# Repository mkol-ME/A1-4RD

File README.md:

# A1-4RD — "Alfred"

A 3D-printed desk companion with a moving jaw and a voice, written in the manner of an old-fashioned
butler: dry, warm, terse, and genuinely useful. Not a smart speaker.

Everything runs locally. A laptop (later a Raspberry Pi inside the printed body) is the face: microphone,
speaker, wake word. A headless Ubuntu box on the LAN is the brain: speech recognition, memory, web lookup,
the language model and his voice. Nothing is sent to a hosted service.

> **The character is the project. Everything else is plumbing.**

## What I built, and what I learned

I built a voice assistant with a fixed personality that runs entirely on my own hardware: speech detection
and wake word on a laptop, and Whisper, a 26-billion-parameter language model, long-term memory, web and
weather lookup and a custom synthesized voice on a home server. That server runs on a secondhand datacenter
GPU I had to reflash and coax into a consumer motherboard. Through measurement rather than guesswork, I got
a spoken reply's first sound down to about 1.15 seconds, and a web-searched answer from 7.1 to 3.5 seconds.
The biggest lesson was that intuition is unreliable with language models. Adding rules to the prompt made
the character worse three separate times. My first test suite passed while the real failures went
undetected, because its questions had leaked into the training examples. Two confident theories about why
he rambled both turned out wrong. So I built a held-out evaluation that checks its own contamination, and
changed things only when a number moved. I also learned to put boundaries in code rather than instructions:
anything that reaches the prompt will eventually be said out loud, so access to memory has to be enforced in
the database query itself.

## The physical build

The body is fully modelled in CAD; it has not been printed or assembled yet.

- **Printed body** ([`hardware/cad/mechanical/rev-b`](hardware/cad/mechanical/rev-b)): sixteen parts as STEP
  solids and millimetre STL, 202 mm tall. The chin is a separate part, driven by a servo through a drive
  link, so the jaw can move while he speaks.
- **Electronics layout** ([`hardware/cad/mechanical/modules-rev-a`](hardware/cad/mechanical/modules-rev-a)):
  a tray and fit models for off-the-shelf boards — Raspberry Pi, I²S microphone, amplifier, servo driver and
  USB-C power.
- **Custom carrier PCB** ([`hardware/cad/pcb/rev-e`](hardware/cad/pcb/rev-e)): a four-layer KiCad board for a
  Pi Zero 2 W, an ICS-43434 microphone, a MAX98357A amplifier and the jaw servo, with a latching power-fault
  cutoff. Gerbers, drill files, BOM and DRC/ERC reports are included; revisions C to E are kept. Not yet
  fabricated.

The STEP files open in SolidWorks, Fusion or FreeCAD. [`hardware/cad/README.md`](hardware/cad/README.md) maps
every revision.

---

## Contents

- [The physical build](#the-physical-build)
- [How a spoken turn works](#how-a-spoken-turn-works)
- [Hardware](#hardware)
- [Repository layout](#repository-layout)
- [Talking to Alfred](#talking-to-alfred)
- [The server](#the-server)
- [Performance](#performance)
- [Testing](#testing)
- [Status and roadmap](#status-and-roadmap)
- [Further reading](#further-reading)

---

## How a spoken turn works

```text
 LAPTOP (client/)                               SERVER (brain/, over an SSH tunnel)
 ─────────────────                              ───────────────────────────────────────────────
 microphone, 16 kHz
   → speech detection against the room's
     measured noise floor
   → at 0.20 s of silence, send audio ────────→ Whisper small.en on the GTX 1060
   → at 0.40 s, end the turn — or wait up to
     1.0 s if the words so far trail off
   → wake word / attention window
   → text ────────────────────────────────────→ voice server
                                                  → tool gate: does this need a lookup?
                                                  → decider: search memory / search web
                                                    (SearXNG, Wikipedia) / sports scores
                                                    (ESPN) / news (Google News) / remember
                                                    weather goes to Open-Meteo instead
                                                  → gemma4 26B on the MI50 via Ollama
                                                  → cut the stream into whole sentences
                                                  → Alfred's distilled Piper voice (CPU)
 speaker (WASAPI) ←──── one WAV per sentence ─── ← streamed as NDJSON
```

The pieces are deliberately separable:

| Layer | Files | Decides |
|---|---|---|
| **Character** | `persona/` (private; `.example` stand-ins here), `brain/prompts.py` | how he behaves |
| **Knowledge** | `brain/memory.py`, `brain/memory_tools.py`, `brain/web.py`, `brain/weather.py`, `brain/sports.py`, `brain/news.py`, `brain/markets.py` | what evidence he sees |
| **Transport** | `brain/voice_server.py`, `brain/whisper_server.py`, SSH | how text and audio move |
| **Embodiment** | `client/listen.py`, `client/talk.py`, later the servos | how he is present in the room |

A better voice cannot fix a bad answer, and a longer prompt cannot replace memory, so each layer is
debugged on its own.

---

## Hardware

**Server** (headless Ubuntu 24.04; setup and operation in [docs/server.md](docs/server.md))

| Part | Role |
|---|---|
| i7-8700 · 48 GB DDR4 · MSI MPG Z390 Gaming Plus | host |
| **AMD Radeon Instinct MI50 32 GB** | the language model (Ollama, Vulkan backend) |
| **NVIDIA GTX 1060 6 GB** | Whisper |
| 500 GB NVMe · 3×2 TB RAID 5 · 1.5 TB | OS and models · Alfred's memory database · spare |

The MI50 is a secondhand datacenter card. Getting it working in a consumer board took a VBIOS reflash,
*Above 4G Decoding* in the BIOS and `pci=realloc` on the kernel command line. It has no fan of its own, so a
server fan is driven from the card's temperature by [`ops/fan`](ops/fan). Two driver settings keep the whole
model in video memory; without them half of it silently spilled into system RAM, at 4 tokens a second
instead of 40 ([why each setting is there](docs/server.md#ollama-settings)).

**Client:** any Windows laptop with a microphone. Later: a Raspberry Pi in the printed body, with a servo jaw
and a neck servo — see [The physical build](#the-physical-build).

---

## Repository layout

```text
A1-4RD/
├── brain/                    runs on the server
│   ├── alfred.py             model choice, prompt assembly, streaming; also a terminal chat client
│   ├── memory.py             SQLite memory: recent conversation, facts, semantic search
│   ├── memory_tools.py       the tool decider and its tools (memory, web, facts)
│   ├── web.py                Wikipedia + SearXNG lookup, run concurrently
│   ├── sports.py             live scores, results and fixtures from ESPN
│   ├── news.py               headlines from Google News
│   ├── markets.py            live prediction-market odds from Polymarket
│   ├── machine.py            the server's own temperatures, fan, power, VRAM, RAID and disks
│   ├── weather.py            live forecast from Open-Meteo, not search snippets
│   ├── media.py              "play…" / "find videos of…" requests and spoken titles
│   ├── media_server.py       YouTube search, audio stream, chapters and captions (own venv: yt-dlp, PyAV)
│   ├── guru.py               The MMA Guru's take on a fight, from his breakdown videos
│   ├── voice_server.py       one spoken turn end to end, streamed sentence by sentence
│   ├── whisper_server.py     resident Whisper, so no model load per utterance
│   ├── audio_archive.py      every utterance kept on the array with its transcript, under a size cap
│   ├── youtube.py            what a named YouTube channel has posted, from its real upload list
│   ├── spoken.py             text rules for what is said aloud, such as which voice reads a sentence
│   ├── prompts.py            loads the private wording, or the .example stand-ins
│   └── whisper_transcribe.py one-off file transcription
├── persona/
│   ├── alfred.example.md     stand-in for alfred.md (who he is), which is kept private
│   ├── examples.example.md   stand-in for examples.md (how he talks)
│   └── prompts.example.json  stand-in for prompts.json (the instructions sent with each turn)
├── client/                   runs on the laptop
│   ├── listen.py             speak to him: wake word, attention window, early transcription
│   ├── talk.py               type to him, hear him answer; also the audio player
│   ├── music.py              plays YouTube audio; pause, stop, volume, ducking under his voice
│   └── launcher/             builds Alfred.exe, a double-click launcher
├── scripts/                  server launch scripts, and a scratch copy of the voice server for testing
├── voice-training/           how his voice was made: auditions, RVC, distillation into Piper
├── tests/                    unit tests for memory, tool gate and the listening loop
├── ops/                      server setup, version-controlled
│   ├── fan/                  MI50 fan curve service + interactive installer
│   ├── reboot/               idle-only 3 a.m. reboot every third night
│   ├── ollama/               Ollama settings and boot-time model preload
│   ├── services/             start SearXNG, Whisper and the voice server at boot
│   └── remote-access/        key-only SSH and Tailscale
├── requirements/             pinned environments (client TTS, Whisper, RVC, Qwen-TTS)
├── hardware/                 CAD (STEP/STL), KiCad PCB and bring-up notes for the body
└── docs/                     running the server, and reaching it
```

---

## Talking to Alfred

- Say **"Alfred, …"** to start. He then stays attentive for three minutes without needing his name.
  **"That'll be all"** dismisses him.
- Say his name while he is talking and he stops, so you can cut in.
- **"Play …"** asks whether you want Spotify or YouTube, then plays it through his speaker. **"Find videos
  of …"** reads out the top results. While music plays, **"Alfred, pause / resume / stop / louder / quieter"** works, and the
  music drops whenever he talks.
- Ask about the weather, last night's game, the news, or something you told him last week. He decides
  on his own when a question needs a lookup.
- Typing works too: the same conversation and memory, without the audio.

Running the client and the server is covered in [docs/server.md](docs/server.md).

---

## Performance

Measured 2026-09-16, from the end of speech to Alfred's first sound, with real audio through the whole
pipeline:

| Turn | Before the MI50 work | Now |
|---|---|---|
| Plain conversation ("why do my prints warp") | 1.5 s | **≈ 1.15 s** |
| Needs the tool decider ("what should I have for dinner") | 4.2 s | **≈ 1.6 s** |
| Memory lookup ("what did I tell you about…") | 4.5 s | **≈ 1.9 s** |
| Web search, real answer (holding line at ≈ 1.0 s) | 7.1 s | **≈ 3.5 s** |

**Model choice.** Candidates run on the MI50 with Alfred's real prompt:

| Model | First sentence | Speed | Character eval |
|---|---|---|---|
| **gemma4:26b Q8** (in use) | **0.43 s** | 41 tok/s | **75/78** |
| gemma4:31b | 1.61 s | 15 tok/s | 77/78 |
| qwen3.6:35b-a3b | 1.35 s | 54 tok/s | 75/78 |
| qwen3.8:27b | 5.50 s | 17 tok/s | — |
| qwen3.5:9b (previous) | 1.77 s | 63 tok/s | 67/78 |

The Qwen 3.x models re-read the whole persona on every turn; Gemma reuses the cached prefix, which is most of
the gap. `gemma4:31b` is the alternative if character ever matters more than speed — one line in
`brain/alfred.py`.

---

## Testing

The unit tests cover memory, the tool gate, the listening loop (segmentation, wake word, unfinished
sentences), the spoken-reply rules, the voice EQ and each lookup's parsing. They need no GPU or model, and
[run on every push](https://github.com/mkol-ME/A1-4RD/actions/workflows/tests.yml):

```bash
pip install numpy scipy sounddevice
python -m unittest discover -s tests
```

The character, conversation and routing evaluations are built on the private persona and real
conversations, so they are kept out of this repository along with it.

---

## Status and roadmap

**Done**
- The persona, and the full voice pipeline: ears, memory, lookups, voice
- MI50 bring-up and latency work; services that start at boot; remote access over Tailscale
- Live weather, sports, news and web search; spoken corrections
- Music from YouTube or Spotify, ducked under his voice; cutting in by saying his name
- A typed client sharing the same conversation and memory
- Optional tools loaded from outside the repository, which can report back when a long job finishes
- The printed body and the carrier PCB, designed in CAD

**Next**
- Recognising who is speaking, with separate memory per person (enforced in SQL, never in the prompt)
- Small character faults — through example curation, not more rules
- A bench prototype of the electronics ([plan](hardware/bringup-plan.md))

**Later:** the Raspberry Pi client inside the printed body, with the servo jaw and neck; timers and alarms
that still ring when the network is down.

---

## Further reading

- [docs/server.md](docs/server.md) — running the client and the server
- [docs/SSH.md](docs/SSH.md) — reaching the server
- [hardware/](hardware) — the physical build

## License

The code is released under the [MIT License](LICENSE). The Adafruit board files in
[`hardware/cad/mechanical/modules-rev-a/source/board-sources`](hardware/cad/mechanical/modules-rev-a/source/board-sources)
keep their own CC BY-SA licence.

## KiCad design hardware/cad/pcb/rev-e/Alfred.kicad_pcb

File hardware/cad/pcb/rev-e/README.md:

# Alfred carrier - revision E

Native KiCad 10 project for Pi Zero 2 W, ICS-43434 microphone, MAX98357A amplifier and one FS90 servo. Revision E replaces D for the next prototype evaluation. Purchasing is deferred.

- R107: verified 32.0k 0.1% part, with recalculated supervisor thresholds.
- R101: Pi/audio current limit lowered from about3.33A to2.02A nominal.
- C101:10nF; slower Pi/audio startup reduces nominal reservoir charging surge from0.94A to0.44A.
- External requirements now include the Pi, microSD, stencil/assembly and enclosure/linkage.

The supported design target is <=1.65A Pi/audio and <=0.80A servo; the earlier4.1A operating allocation is withdrawn. This is a deliberate reduction in supported load, not proof that all power-margin concerns are resolved. Read Power-acceptance.md. It includes source-voltage/path-loss criteria and tests that still require built hardware. The hardware latch still prevents restart after a detected fault until a deliberate new command edge.

Open Alfred.kicad_pro. Use the current BOM, Gerbers, assembly instructions and drawings together. Validation.txt records the completed CAD and offline checks. No physical board or target audio software has been tested; prototype power qualification is still open. Do not describe this release as production-qualified.

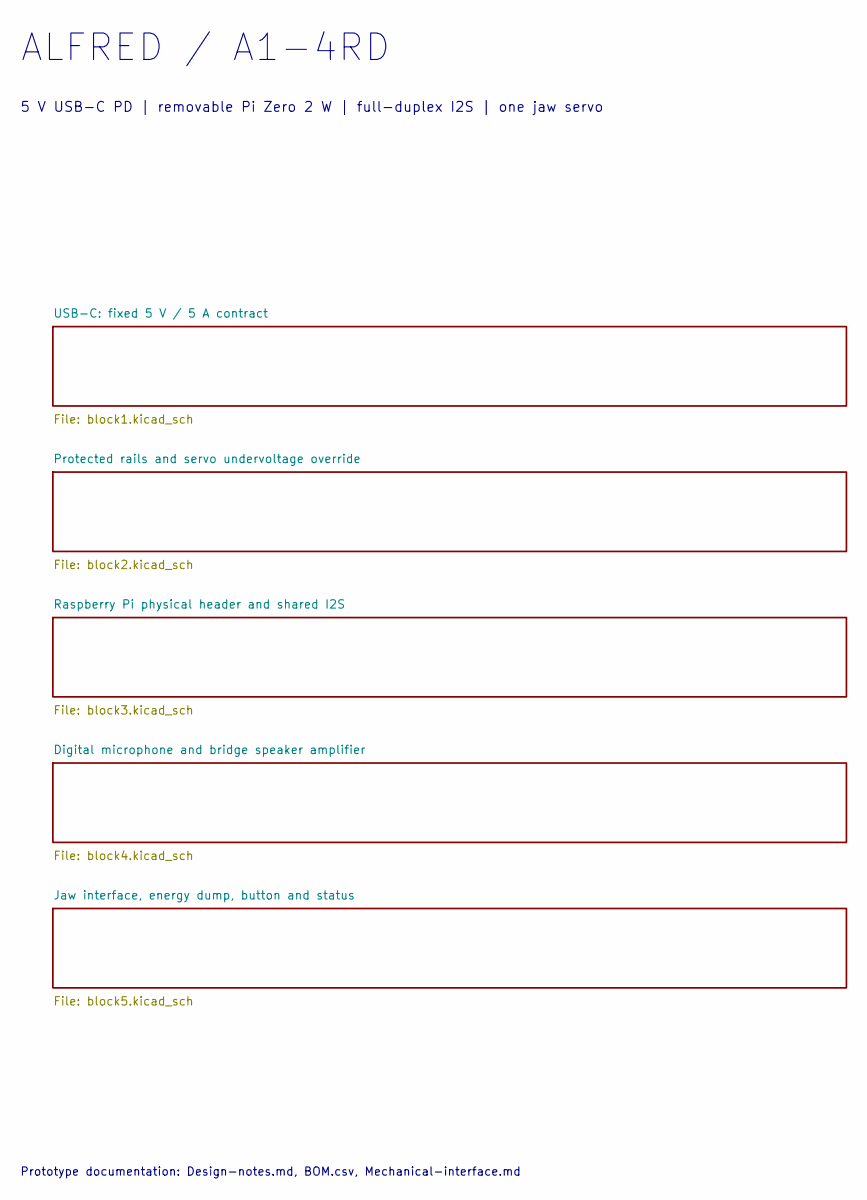
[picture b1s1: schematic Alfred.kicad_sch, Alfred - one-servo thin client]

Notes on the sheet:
ALFRED / A1-4RD
Prototype documentation: Design-notes.md, BOM.csv, Mechanical-interface.md
5 V USB-C PD | removable Pi Zero 2 W | full-duplex I2S | one jaw servo

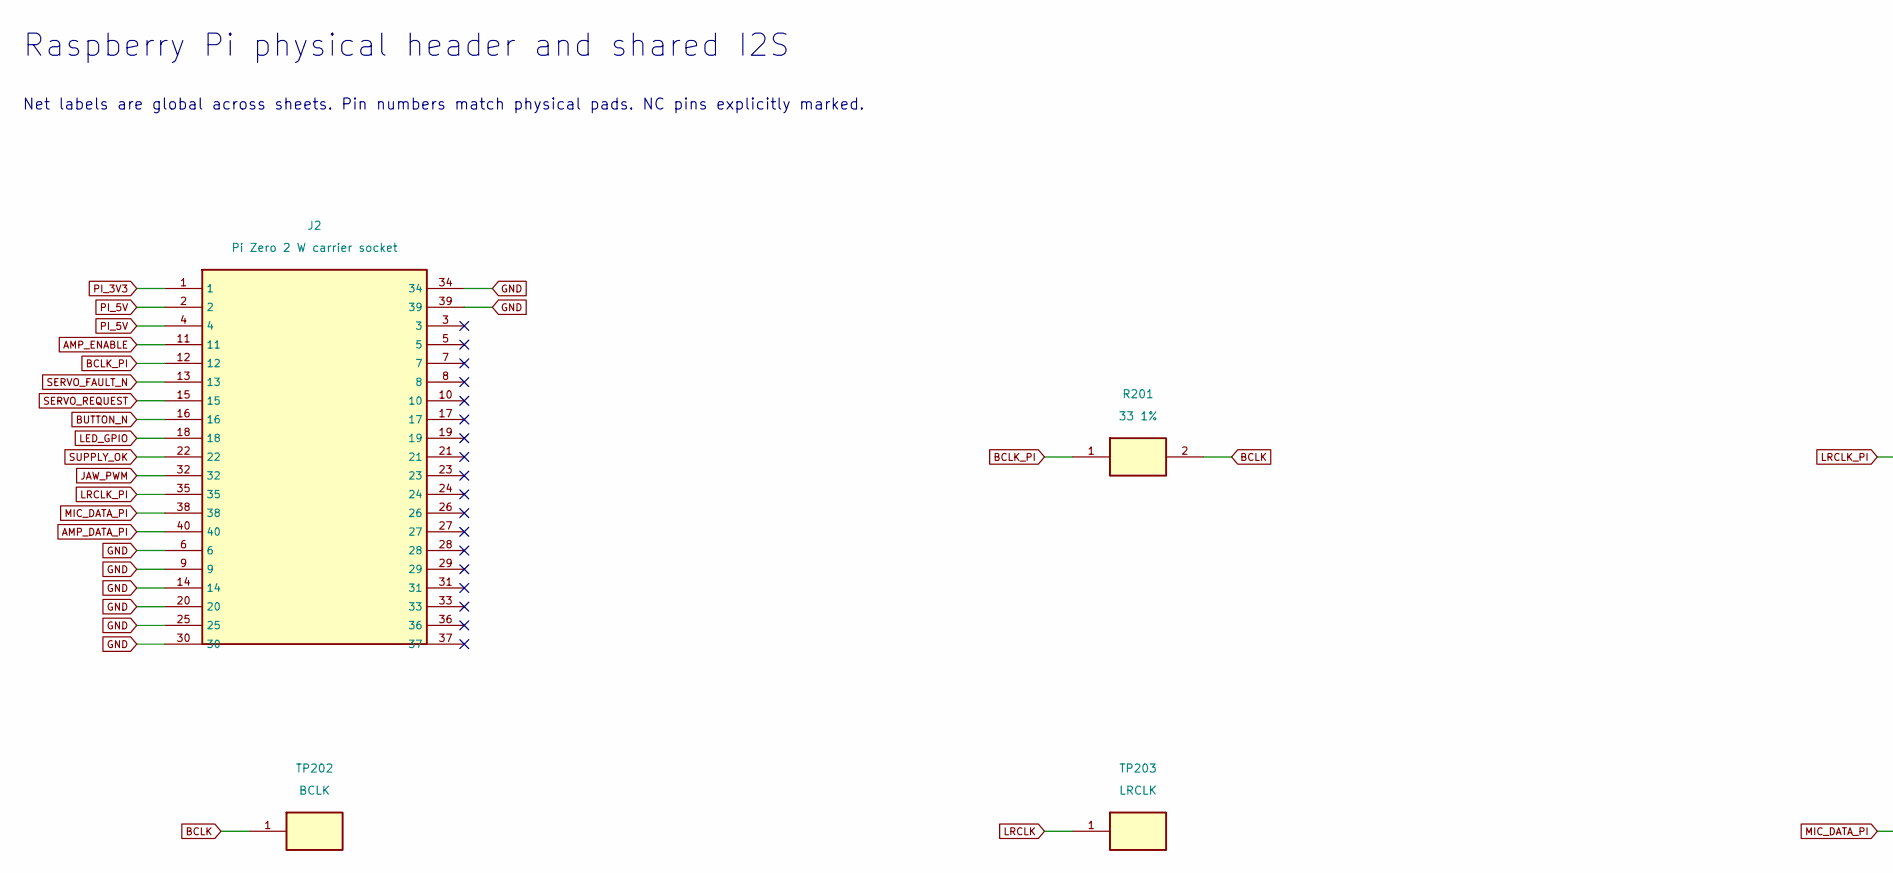
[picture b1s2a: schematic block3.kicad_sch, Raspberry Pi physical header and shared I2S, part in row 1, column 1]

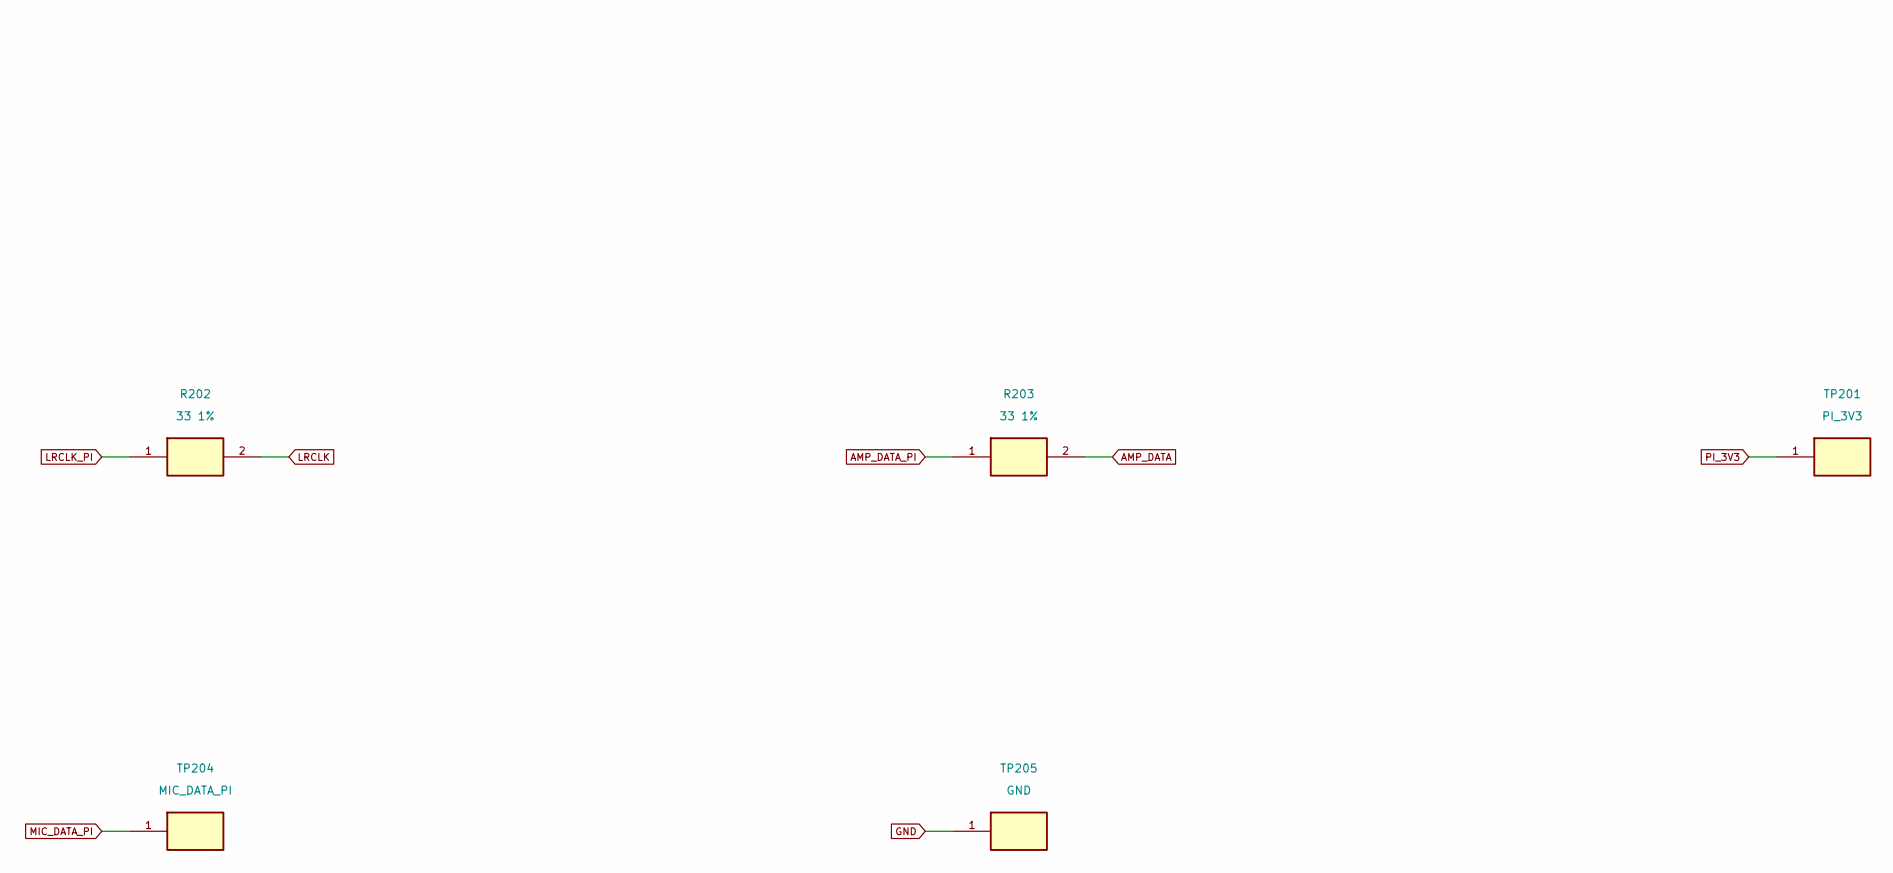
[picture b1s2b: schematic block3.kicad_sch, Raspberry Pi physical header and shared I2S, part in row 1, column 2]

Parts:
J2: Pi Zero 2 W carrier socket; PinSocket_2x20_P2.54mm_Vertical; MPN SSW-120-01-G-D
R201, R202, R203: 33 1%; R_0805_2012Metric; MPN RC0805FR-0733RL
TP201: PI_3V3; TestPoint_Pad_D1.5mm; MPN PCB copper test point
TP202: BCLK; TestPoint_Pad_D1.5mm; MPN PCB copper test point
TP203: LRCLK; TestPoint_Pad_D1.5mm; MPN PCB copper test point
TP204: MIC_DATA_PI; TestPoint_Pad_D1.5mm; MPN PCB copper test point
TP205: GND; TestPoint_Pad_D1.5mm; MPN PCB copper test point

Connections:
AMP_DATA: R203.2; also elsewhere on the board
AMP_DATA_PI: J2.40, R203.1
AMP_ENABLE: J2.11; also elsewhere on the board
BCLK: R201.2, TP202.1; also elsewhere on the board
BCLK_PI: J2.12, R201.1
BUTTON_N: J2.16; also elsewhere on the board
GND: J2.6, J2.9, J2.14, J2.20, J2.25, J2.30, J2.34, J2.39, TP205.1; also elsewhere on the board
JAW_PWM: J2.32; also elsewhere on the board
LED_GPIO: J2.18; also elsewhere on the board
LRCLK: R202.2, TP203.1; also elsewhere on the board
LRCLK_PI: J2.35, R202.1
MIC_DATA_PI: J2.38, TP204.1; also elsewhere on the board
PI_3V3: J2.1, TP201.1; also elsewhere on the board
PI_5V: J2.2, J2.4; also elsewhere on the board
SERVO_FAULT_N: J2.13; also elsewhere on the board
SERVO_REQUEST: J2.15; also elsewhere on the board
SUPPLY_OK: J2.22; also elsewhere on the board

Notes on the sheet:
Net labels are global across sheets. Pin numbers match physical pads. NC pins explicitly marked.
Raspberry Pi physical header and shared I2S

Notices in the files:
README.md:
license: MIT
